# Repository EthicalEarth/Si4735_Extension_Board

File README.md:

# Si4735_Extension_Board
There you can find PCB-Projects to build a control and front boards for SI4735 Radio. Please be careful, these Projects are absolutely alpha-version. The circuits can be wrong or have mistake..

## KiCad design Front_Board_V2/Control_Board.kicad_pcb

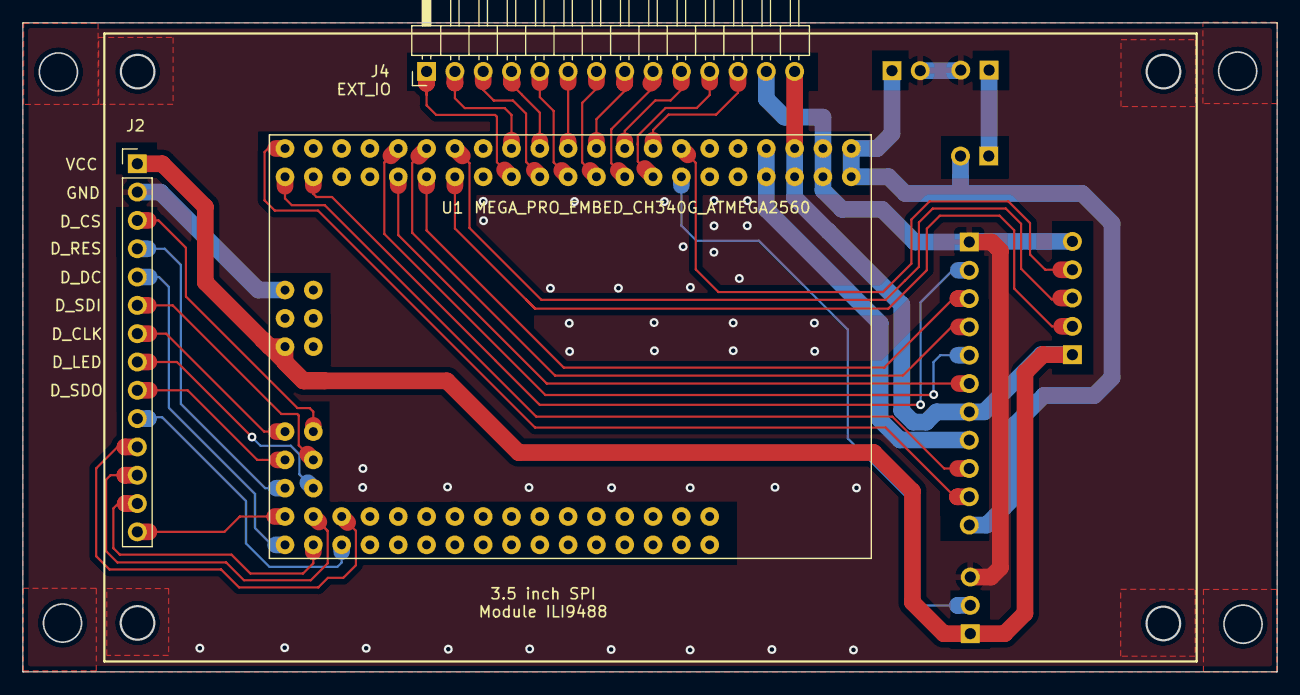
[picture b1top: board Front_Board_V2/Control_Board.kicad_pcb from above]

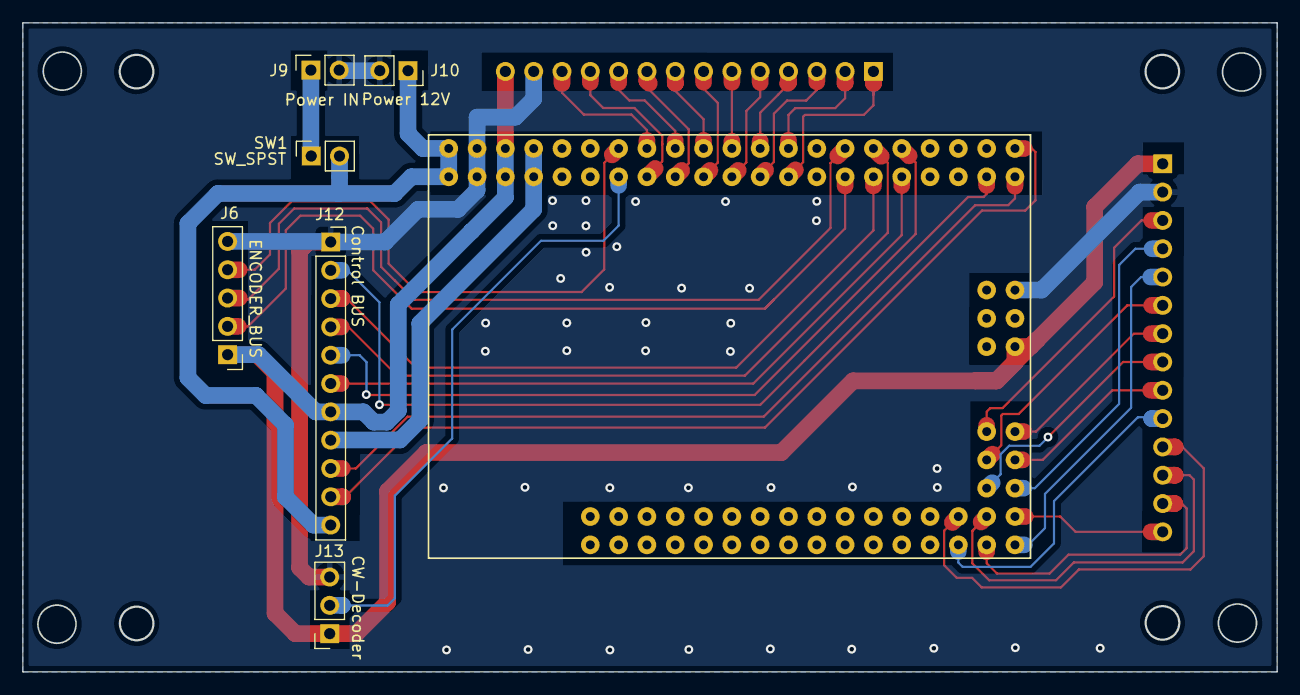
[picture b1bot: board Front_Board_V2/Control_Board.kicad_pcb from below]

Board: 2 copper layers, 112.5 x 58.2 mm, 9 parts (6 on the bottom side), 40 nets.

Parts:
J2: 14_pin_3.5_ILI9488; PinHeader_1x14_P2.54mm_Vertical
J4: EXT_IO; PinHeader_1x14_P2.54mm_Horizontal
J6: ENCODER_BUS; PinHeader_1x05_P2.54mm_Vertical
J9: Power IN; PinSocket_1x02_P2.54mm_Vertical
J10: Power 12V; PinSocket_1x02_P2.54mm_Vertical
J12: Control BUS; PinSocket_1x11_P2.54mm_Vertical
J13: CW-Decoder; PinSocket_1x03_P2.54mm_Vertical
SW1: SW_SPST; PinSocket_1x02_P2.54mm_Vertical
U1: MEGA_PRO_EMBED_CH340G_ATMEGA2560; MODULE_MEGA_PRO_EMBED_CH340G_ATMEGA2560

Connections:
3.3V: J12.8, U1.3V3_1 (3V3), U1.3V3_2 (3V3)
12V: J10.1, J12.11, SW1.2 (B), U1.VIN_1 (VIN), U1.VIN_2 (VIN)
A_RST: J12.6, U1.D22
A_SCL: J12.4, U1.D21
A_SDA: J12.3, U1.D20
A_SEN: J12.5, U1.D23
D4: J4.11, U1.D4
D5: J4.12, U1.D5
D6: J4.9, U1.D6
D7: J4.10, U1.D7
D8: J4.7, U1.D8
D9: J4.8, U1.D9
D10: J4.5, U1.D10
D11: J4.6, U1.D11
D12: J4.3, U1.D12
D13: J4.4, U1.D13
D14: J4.1, U1.D14
D15: J4.2, U1.D15
DECODER: J13.2, U1.D2
D_CLK: J2.7, U1.D52
D_CS: J2.3, U1.D53
D_DC(RS): J2.5, U1.D46
D_LED: J2.8, U1.D49
D_RES: J2.4, U1.D48
D_SDA(SDI): J2.6, U1.D51
D_SDO: J2.9, U1.D50
ENC_A: J6.2, U1.D18
ENC_B: J6.3, U1.D19
ENC_P: J6.4, U1.D3
GND: J2.2, J4.13, J6.5, J9.2, J10.2, J12.1, J13.3, U1.GND_1 (GND), U1.GND_2 (GND), U1.GND_3 (GND)
I2C-SW: J12.2, U1.D28
Mute: J12.10, U1.D31
unnamed: J9.1, SW1.1 (A)
Sleep: J12.9, U1.D30
T_CLK: J2.10, U1.D42
T_CS: J2.11, U1.D43
T_DIN: J2.12, U1.D45
T_DO: J2.13, U1.D44
T_IRQ: J2.14, U1.D47
VCC_5V: J2.1, J4.14, J6.1, J12.7, J13.1, U1.5V_1 (5V), U1.5V_2 (5V), U1.5V_3 (5V)

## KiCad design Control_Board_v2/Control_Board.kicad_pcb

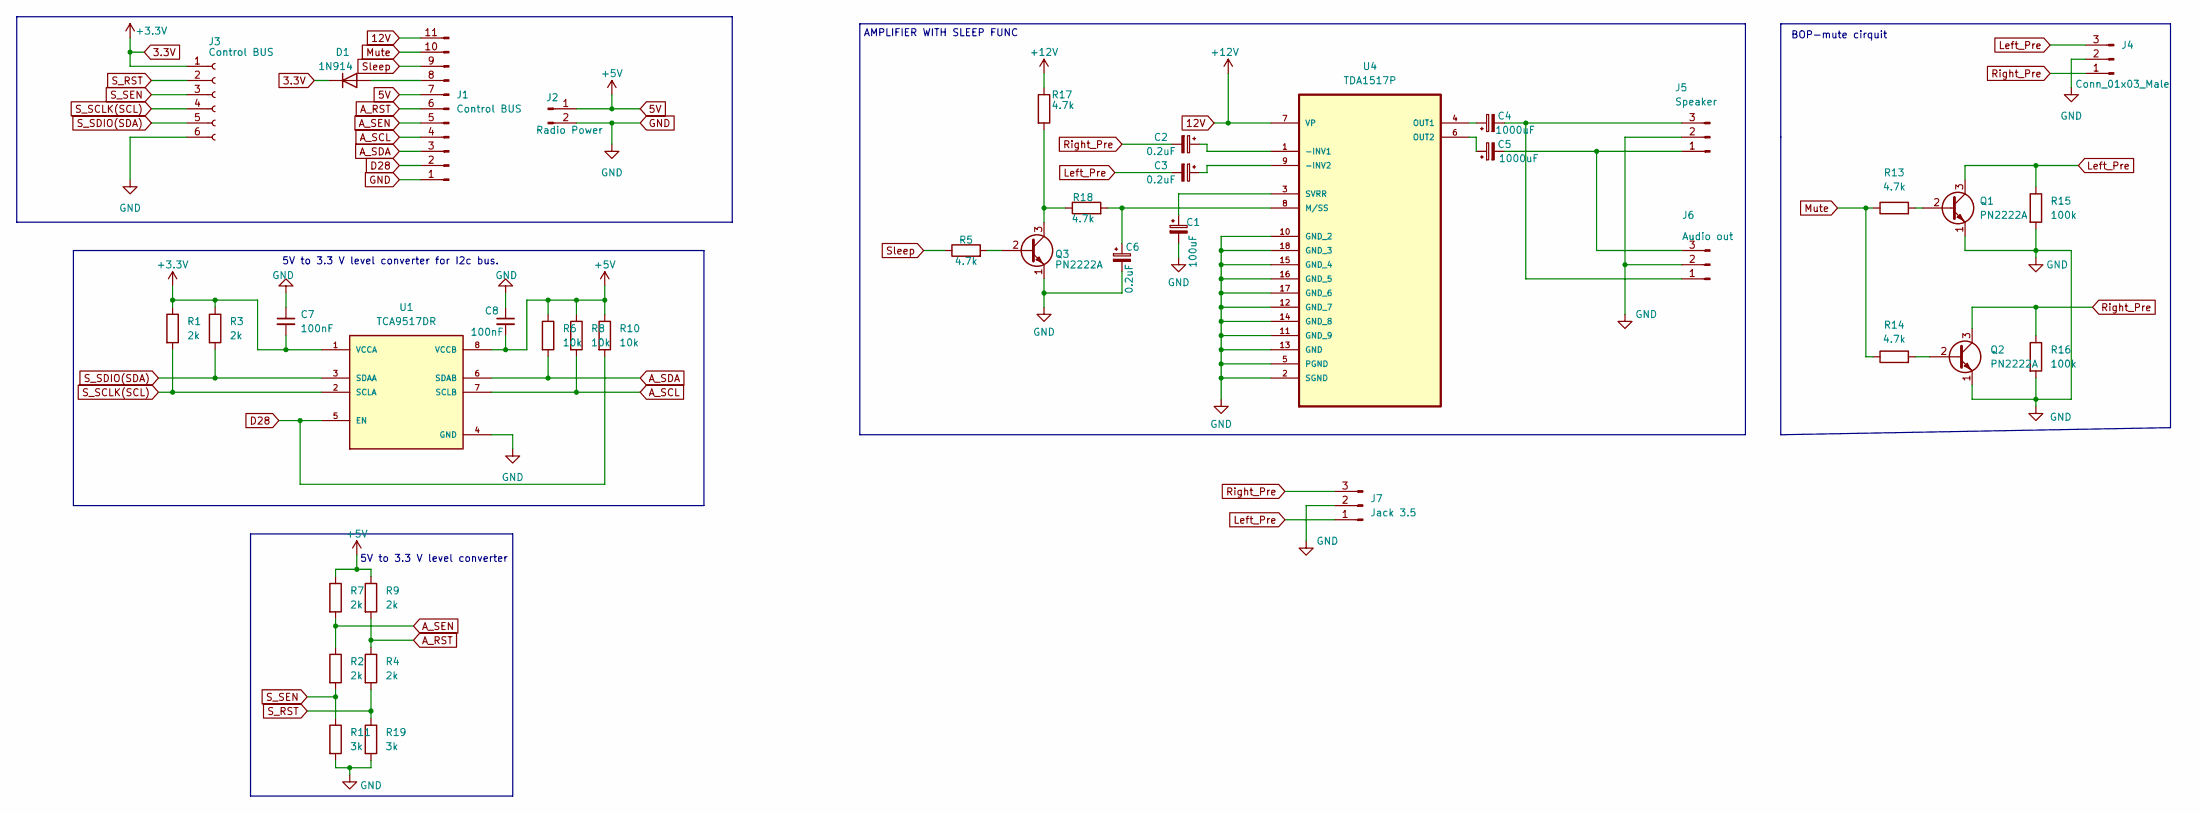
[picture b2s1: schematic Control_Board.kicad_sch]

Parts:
C1: 100uF; CP_Radial_D5.0mm_P2.00mm
C2, C3, C6: 0.2uF; CP_Radial_D4.0mm_P2.00mm
C4, C5: 1000uF; CP_Radial_D8.0mm_P3.80mm
C7, C8: 100nF; C_1206_3216Metric
D1: 1N914; D_DO-35_SOD27_P7.62mm_Horizontal
J1: Control BUS; PinSocket_1x11_P2.54mm_Vertical
J2: Radio Power; PinSocket_1x02_P2.54mm_Vertical
J3: Control BUS; PinSocket_1x06_P2.54mm_Vertical
J4: Conn_01x03_Male; PinSocket_1x03_P2.54mm_Vertical
J5: Speaker; PinSocket_1x03_P2.54mm_Vertical
J6: Audio out; PinSocket_1x03_P2.54mm_Vertical
J7: Jack 3.5; PinSocket_1x03_P2.54mm_Vertical
Q1, Q2, Q3: PN2222A; TO-92_Inline
R1, R2, R3, R4, R7, R9: 2k; R_1206_3216Metric
R5, R13, R14, R17, R18: 4.7k; R_1206_3216Metric
R6, R8, R10: 10k; R_1206_3216Metric
R11, R19: 3k; R_1206_3216Metric
R15, R16: 100k; R_1206_3216Metric
U1: TCA9517DR; SOIC127P599X175-8N; PARTREV D
U4: TDA1517P; DIP254P762X470-18; MPN TDA1517P/N3,112

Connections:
3.3V: C7.2, D1.1 (K), J3.1, R1.1, R3.1, U1.1 (VCCA)
5V: C8.2, J1.7, J2.1, R6.1, R7.1, R8.1, R9.1, R10.1, U1.8 (VCCB)
12V: J1.11, R17.1, U4.7 (VP)
A_RST: J1.6, R4.1, R9.2
A_SCL: J1.4, R8.2, U1.7 (SCLB)
A_SDA: J1.3, R6.2, U1.6 (SDAB)
A_SEN: J1.5, R2.1, R7.2
D28: J1.2, R10.2, U1.5 (EN)
GND: C1.2, C6.2, C7.1, C8.1, J1.1, J2.2, J3.6, J4.2, J5.2, J6.2, J7.2, Q1.1 (E), Q2.1 (E), Q3.1 (E), R11.2, R15.2, R16.2, R19.2, U1.4 (GND), U4.2 (SGND), U4.5 (PGND), U4.10 (GND_2), U4.11 (GND_9), U4.12 (GND_7), U4.13 (GND), U4.14 (GND_8), U4.15 (GND_4), U4.16 (GND_5), U4.17 (GND_6), U4.18 (GND_3)
Left_Pre: C3.2, J4.3, J7.1, Q1.3 (C), R15.1
Mute: J1.10, R13.1, R14.1
unnamed: C1.1, U4.3 (SVRR)
unnamed: C2.1, U4.1 (-INV1)
unnamed: C3.1, U4.9 (-INV2)
unnamed: C4.1, U4.4 (OUT1)
unnamed: C4.2, J5.3, J6.1
unnamed: C5.1, U4.6 (OUT2)
unnamed: C5.2, J5.1, J6.3
unnamed: C6.1, R18.2, U4.8 (M/SS)
unnamed: D1.2 (A), J1.8
unnamed: Q1.2 (B), R13.2
unnamed: Q2.2 (B), R14.2
unnamed: Q3.2 (B), R5.2
unnamed: Q3.3 (C), R17.2, R18.1
Right_Pre: C2.2, J4.1, J7.3, Q2.3 (C), R16.1
S_RST: J3.2, R4.2, R19.1
S_SCLK(SCL): J3.4, R1.2, U1.2 (SCLA)
S_SDIO(SDA): J3.5, R3.2, U1.3 (SDAA)
S_SEN: J3.3, R2.2, R11.1
Sleep: J1.9, R5.1

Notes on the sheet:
5V to 3.3 V level converter
BOP-mute cirquit
AMPLIFIER WITH SLEEP FUNC
5V to 3.3 V level converter for I2c bus.

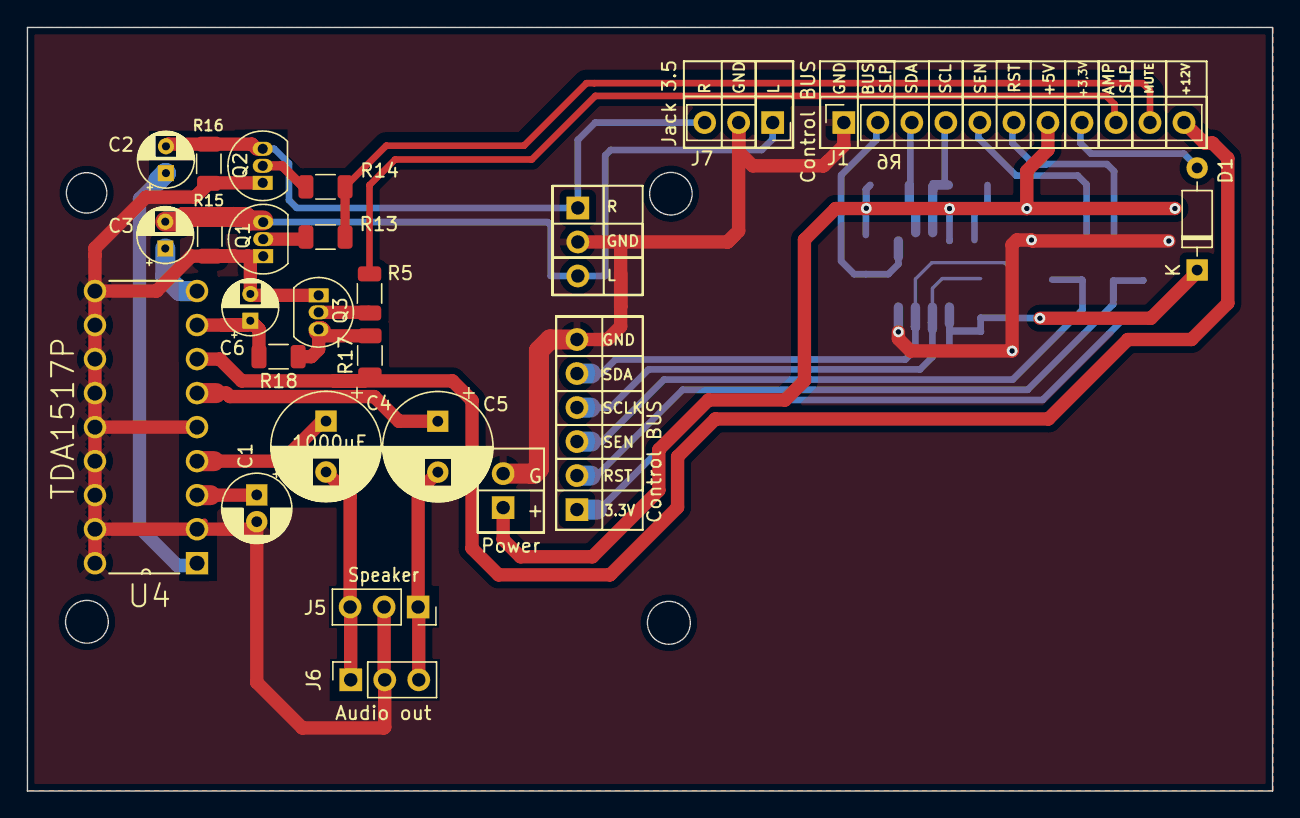
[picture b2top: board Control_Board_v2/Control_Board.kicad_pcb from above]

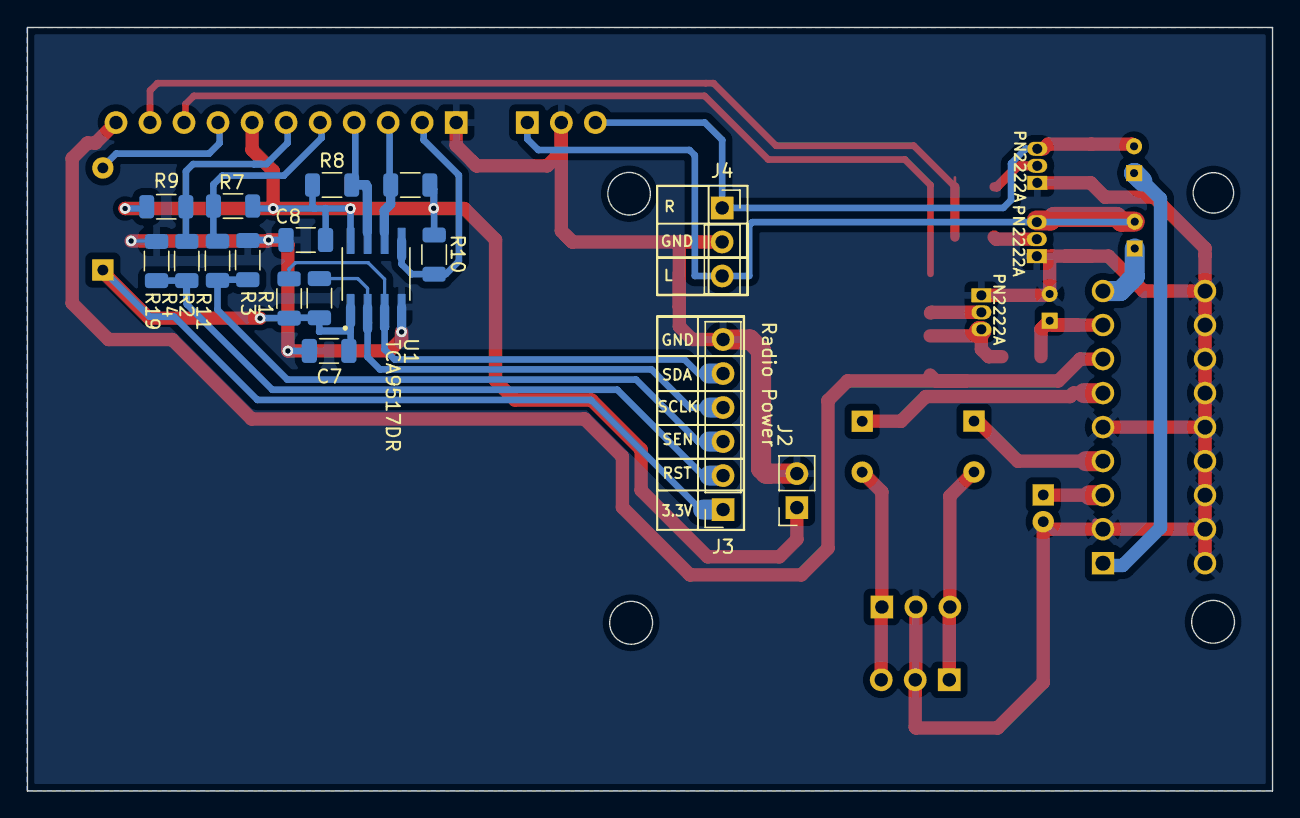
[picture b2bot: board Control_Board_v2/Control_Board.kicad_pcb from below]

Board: 2 copper layers, 93.0 x 57.0 mm, 39 parts (17 on the bottom side), 30 nets.

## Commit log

2023-04-16 DESCRIBE COMMIT IN A FEW WORDS
2023-11-05 Initial release.
